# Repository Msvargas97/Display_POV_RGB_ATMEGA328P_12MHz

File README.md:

Display_POV_RGB_ATMEGA328P_12MHz
Control de display POV RGB v1.1 + Codigo Arduino+Bootloader V-USB

 Código C++ para Proyecto de grado - Tecnico Profesional en Electrónica -UDI

 ALGORITMO
  
  Los pasos para realización del código son los siguientes:
  
  0.Esperar que el sensor de efecto Hall indique el punto de partida de visualización   
  
  1.Se encienden los LEDs según los bits correspondientes de un número en binario
  que hace referencia a una columna de cualquier caracter, ya sea una image,numeros o letras.
  
  2.Gracias a que el timer esta configurado como comparador se asigna un periodo, el cual sera el tiempo que permaneceran
  encendida la columna de LEDs del paso anterior.
  
  3.Apagar los LEDs y repetir el algoritmo desde el paso 0.
  
   Posteriormente se tiene caracteristicas extras que se añaden en cualquiera de los pasos
   mencionados anteriormente segun sea su función,por ejemplo escoger el color de los LEDs
   esto se logra enviando un '1' lógico a la base del transistor que controla el color deseado,
   dicha caracteristica se implemento en el paso 1.

Caracteristicas:

Posee tres modos de operación:
-Modo frases ingresadas por Bluetooth o comunicacion serial.
-Modo visualizador de imagenes cargadas desde la EEPROM
-Modo reloj digital

  Elaborado por Michael Vargas
  
  2015
  
  msvargas97@gmail.com
  
  Open Source GitHub: https://github.com/Msvargas97/Display_POV_RGB_ATMEGA328P_12MHz
  
  Créditos al MiniPOV4 de Adrafuit, por el bootloader y el software para cargar imagenes.
  
  https://github.com/adafruit/Adafruit-MiniPOV4-Kit

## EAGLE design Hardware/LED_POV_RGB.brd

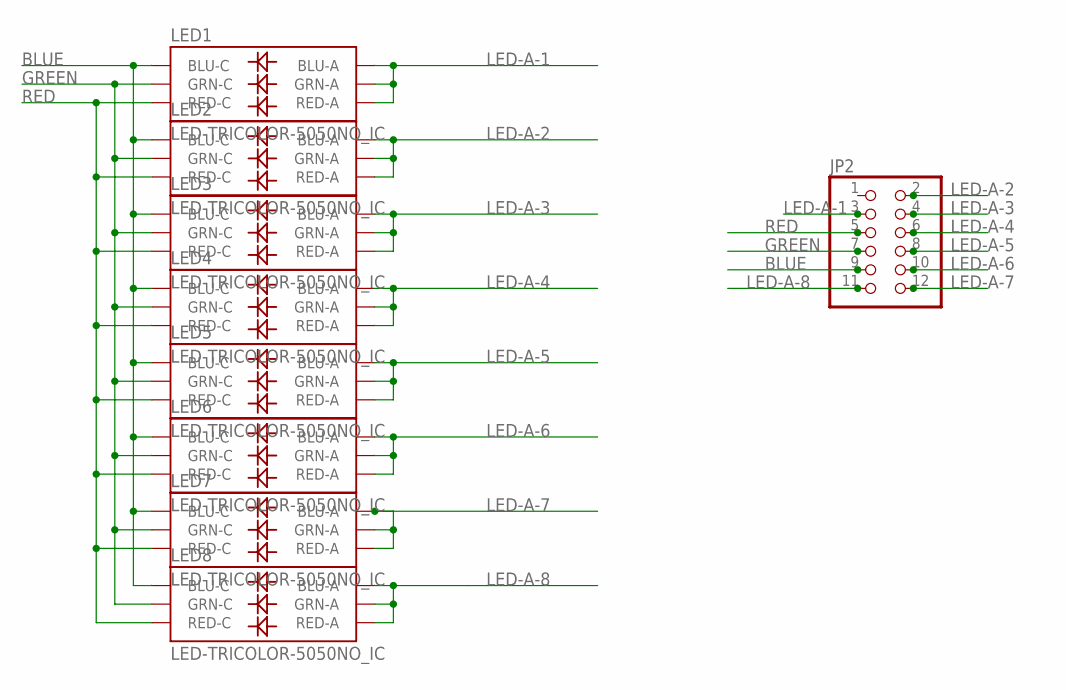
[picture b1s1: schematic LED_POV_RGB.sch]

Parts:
JP2: PINHD-2X6; 2X06
LED1, LED2, LED3, LED4, LED5, LED6, LED7, LED8: LED-TRICOLOR-5050NO_IC; LED-TRICOLOR-5050

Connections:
BLUE: JP2.9, LED1.4 (BLU-C), LED2.4 (BLU-C), LED3.4 (BLU-C), LED4.4 (BLU-C), LED5.4 (BLU-C), LED6.4 (BLU-C), LED7.4 (BLU-C), LED8.4 (BLU-C)
GREEN: JP2.7, LED1.6 (GRN-C), LED2.6 (GRN-C), LED3.6 (GRN-C), LED4.6 (GRN-C), LED5.6 (GRN-C), LED6.6 (GRN-C), LED7.6 (GRN-C), LED8.6 (GRN-C)
LED-A-1: JP2.3, LED1.1 (GRN-A), LED1.2 (RED-A), LED1.3 (BLU-A)
LED-A-2: JP2.2, LED2.1 (GRN-A), LED2.2 (RED-A), LED2.3 (BLU-A)
LED-A-3: JP2.4, LED3.1 (GRN-A), LED3.2 (RED-A), LED3.3 (BLU-A)
LED-A-4: JP2.6, LED4.1 (GRN-A), LED4.2 (RED-A), LED4.3 (BLU-A)
LED-A-5: JP2.8, LED5.1 (GRN-A), LED5.2 (RED-A), LED5.3 (BLU-A)
LED-A-6: JP2.10, LED6.1 (GRN-A), LED6.2 (RED-A), LED6.3 (BLU-A)
LED-A-7: JP2.12, LED7.1 (GRN-A), LED7.2 (RED-A), LED7.3 (BLU-A)
LED-A-8: JP2.11, LED8.1 (GRN-A), LED8.2 (RED-A), LED8.3 (BLU-A)
RED: JP2.5, LED1.5 (RED-C), LED2.5 (RED-C), LED3.5 (RED-C), LED4.5 (RED-C), LED5.5 (RED-C), LED6.5 (RED-C), LED7.5 (RED-C), LED8.5 (RED-C)

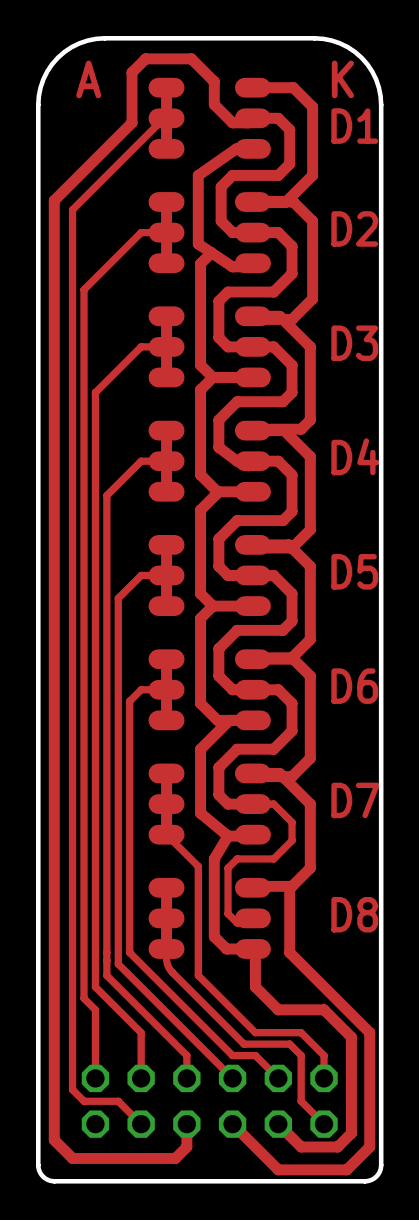
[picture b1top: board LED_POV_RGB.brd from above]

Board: 2 copper layers, 19.1 x 63.5 mm, 9 parts (0 on the bottom side), 11 nets.

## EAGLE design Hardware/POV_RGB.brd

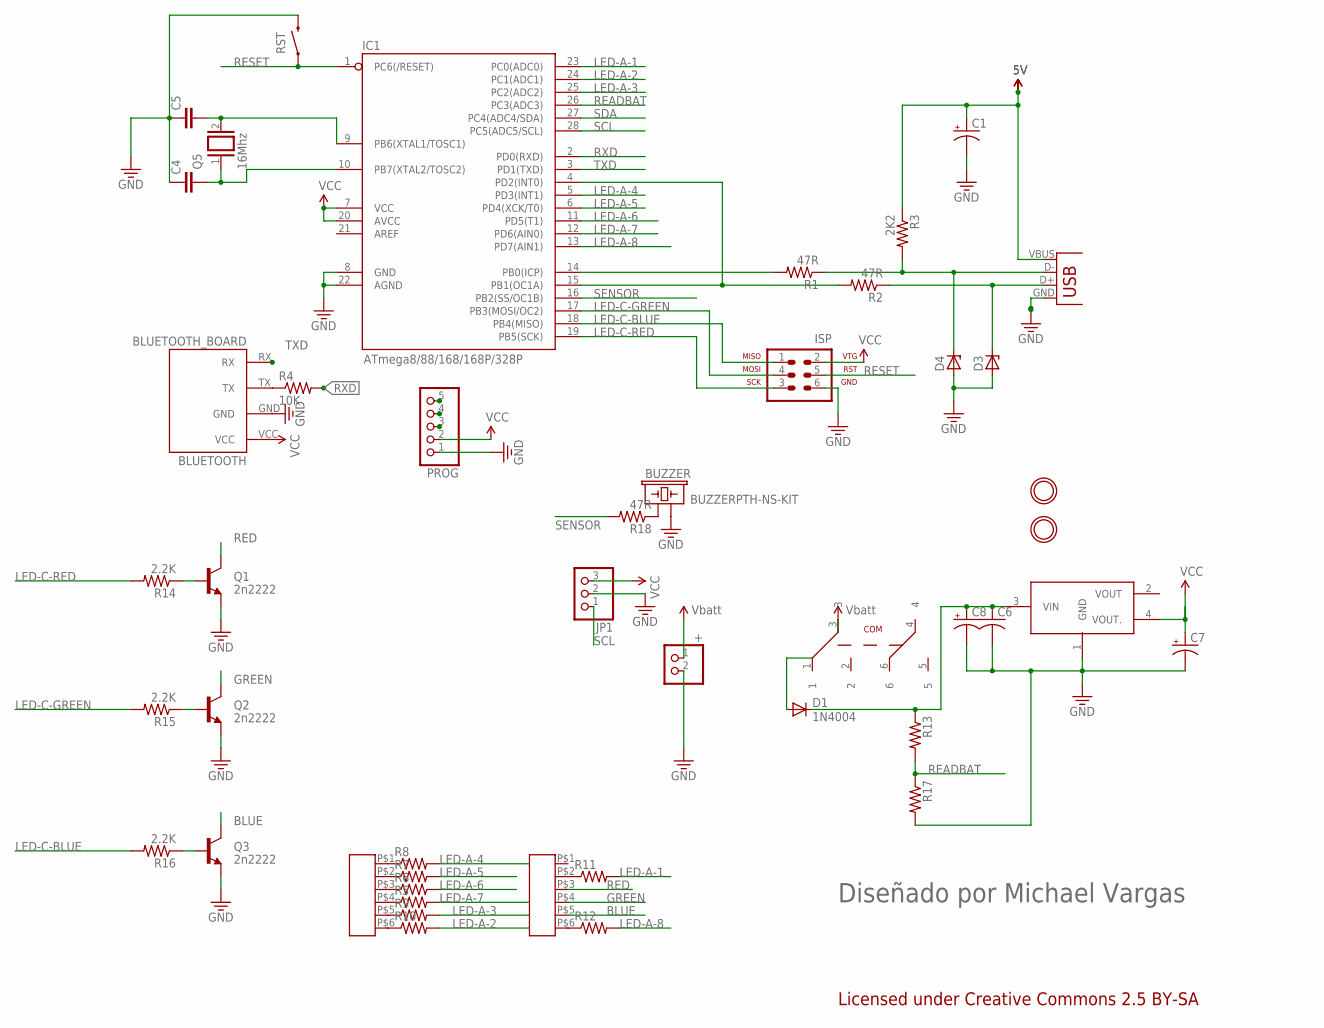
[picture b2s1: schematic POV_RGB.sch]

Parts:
5V: LD1117S50TR; SOT223
+: HEADER-1X2; 1X02_OVAL
BLUETOOTH: BLUETOOTH_BOARD; BT_BOARD_FOOTPRINT
BUZZER: BUZZERPTH-NS-KIT; BUZZER-12MM-NS-KIT
C1, C7, C8: CPOL-USD; PANASONIC_D
C4, C5: CAPPTH2; CAP-PTH-SMALL2
C6: C-USC1206; C1206
D1: 1N4004; DO41-10
D3, D4: ZENER-DIODEDO34-7; DO34Z7
IC1: ATmega8/88/168/168P/328P; DIL28-3
ISP: AVR-ISP-6
JP1: PINHD-1X3; 1X03
PROG: PINHD-1X5; 1X05
Q1, Q2, Q3: 2n2222; TO-92-AMMO
Q5: 16Mhz; QS
R1, R2: 47R; 0207/9
R3: 2K2; 0207/9
R4: 10K; R0805
R5, R6, R7, R8, R9, R10, R11, R12, R13, R17: R-US_R0805; R0805
R14, R15, R16: 2.2K; R0805
R18: 47R; R0805
RST: SWITCH-MOMENTARY-2SMD-1101NE; TACTILE-SWITCH-1101NE
U$2, U$4: MOUNTINGHOLE2.5_THICK; MOUNTINGHOLE_2.5_PLATED_THICK
U$3, U$5: SMD_HEADER6
U$6: TL2285
USB: USBPTH; USB-B-PTH

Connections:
3.3V: +.1, U$6.3
5V: C1.+, R3.1, USB.VBUS
BLUE: Q3.3 (C), U$5.P$5
GND: 5V.1 (GND), +.2, BLUETOOTH.GND, BUZZER.- (2), C1.-, C4.1, C5.1, C6.2, C7.-, C8.-, D3.A, D4.A, IC1.8 (GND), IC1.22 (AGND), ISP.6 (GND), JP1.2, PROG.1, Q1.1 (E), Q2.1 (E), Q3.1 (E), R17.2, RST.2, USB.GND, USB.S1, USB.S2
GREEN: Q2.3 (C), U$5.P$4
LED-A-1: IC1.23 (PC0(ADC0)), R11.2
LED-A-2: IC1.24 (PC1(ADC1)), R10.2
LED-A-3: IC1.25 (PC2(ADC2)), R9.2
LED-A-4: IC1.5 (PD3(INT1)), R8.2
LED-A-5: IC1.6 (PD4(XCK/T0)), R7.2
LED-A-6: IC1.11 (PD5(T1)), R6.2
LED-A-7: IC1.12 (PD6(AIN0)), R5.2
LED-A-8: IC1.13 (PD7(AIN1)), R12.2
LED-C-BLUE: IC1.18 (PB4(MISO)), ISP.1 (MISO), R16.2
LED-C-GREEN: IC1.17 (PB3(MOSI/OC2)), ISP.4 (MOSI), R15.2
LED-C-RED: IC1.19 (PB5(SCK)), ISP.3 (SCK), R14.2
unnamed: R5.1, U$3.P$4
unnamed: 5V.3 (VIN), C6.1, C8.+, D1.C, R13.1
unnamed: D4.C, R1.1, R3.2, USB.D-
unnamed: D3.C, R2.1, USB.D+
unnamed: R6.1, U$3.P$3
unnamed: R7.1, U$3.P$2
unnamed: IC1.14 (PB0(ICP)), R1.2
unnamed: IC1.4 (PD2(INT0)), IC1.15 (PB1(OC1A)), R2.2
unnamed: C5.2, IC1.9 (PB6(XTAL1/TOSC1)), Q5.2
unnamed: R8.1, U$3.P$1
unnamed: R9.1, U$3.P$5
unnamed: R10.1, U$3.P$6
unnamed: R11.1, U$5.P$2
unnamed: R12.1, U$5.P$6
unnamed: BUZZER.+ (1), R18.1
unnamed: Q1.2 (B), R14.1
unnamed: Q2.2 (B), R15.1
unnamed: Q3.2 (B), R16.1
unnamed: C4.2, IC1.10 (PB7(XTAL2/TOSC2)), Q5.1
unnamed: D1.A, U$6.1
unnamed: BLUETOOTH.TX, R4.1
READBAT: IC1.26 (PC3(ADC3)), R13.2, R17.1
RED: Q1.3 (C), U$5.P$3
RESET: IC1.1 (PC6(/RESET)), ISP.5 (RST), PROG.5, RST.1
RXD: IC1.2 (PD0(RXD)), PROG.4, R4.2
SCL: IC1.28 (PC5(ADC5/SCL)), JP1.1
SDA: IC1.27 (PC4(ADC4/SDA))
SENSOR: IC1.16 (PB2(SS/OC1B)), R18.2
TXD: BLUETOOTH.RX, IC1.3 (PD1(TXD)), PROG.3
VCC: 5V.4 (VOUT.), BLUETOOTH.VCC, C7.+, IC1.7 (VCC), IC1.20 (AVCC), ISP.2 (VTG), JP1.3, PROG.2

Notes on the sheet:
Licensed under Creative Commons 2.5 BY-SA
Diseñado por Michael Vargas

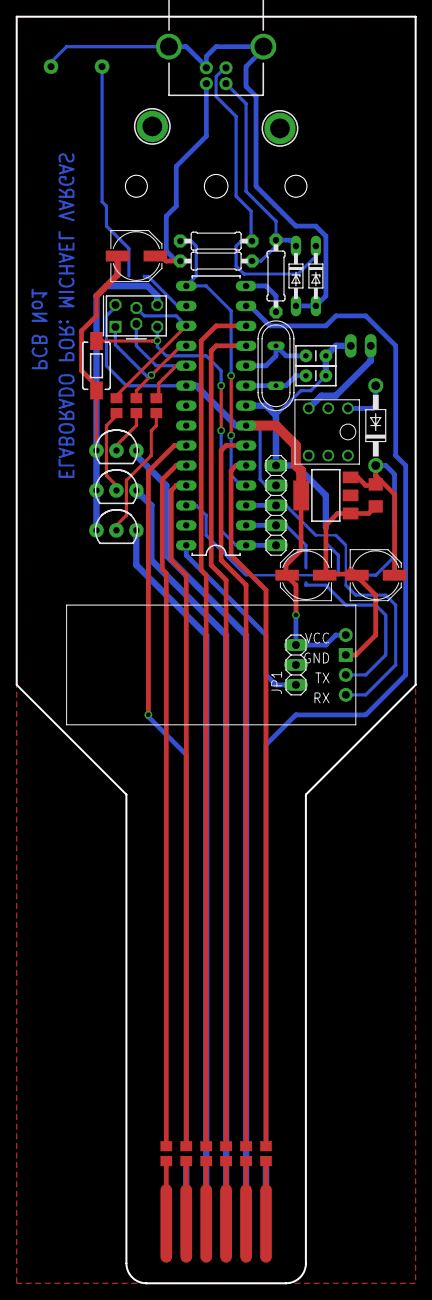
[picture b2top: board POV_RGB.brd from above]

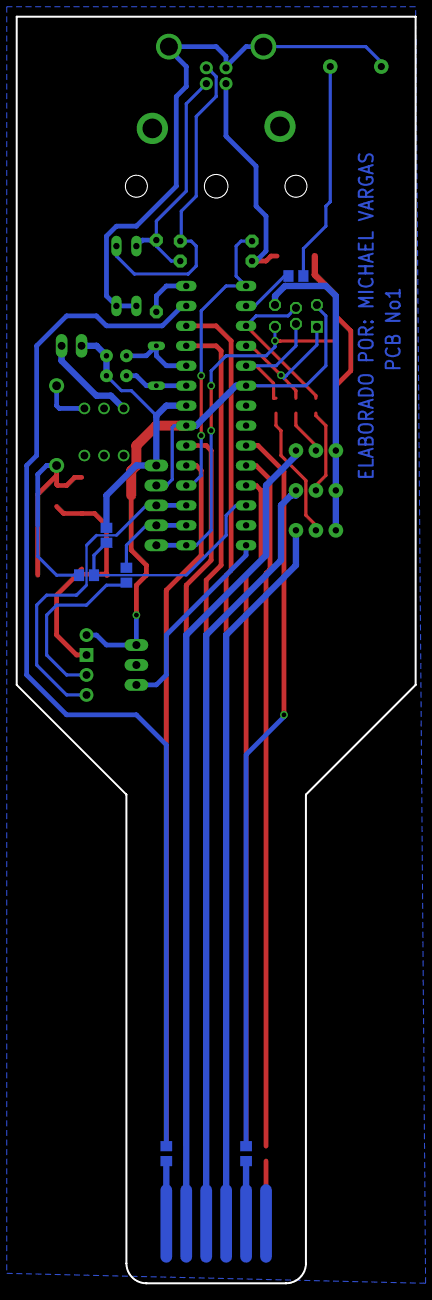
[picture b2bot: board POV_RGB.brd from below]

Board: 2 copper layers, 50.8 x 161.3 mm, 46 parts (7 on the bottom side), 45 nets.

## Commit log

2015-09-27 :tada: Added .gitattributes & .gitignore files
2015-09-27 initi v1.0
    Initial Version
    -Source code base:
    https://github.com/adafruit/Adafruit-MiniPOV4-Kit
    Thanks!
2015-10-12 README.md
    Descripción del proyecto display POV RGB.
    Michael Vargas
    Open Source
2015-10-12 Código debuggeado v1.1
2015-10-13 Archivos Eagle
    Añadido esquematicos y boards para la elaboración de las PCBs.
2015-11-19 Código POV RGB Depurado Full
    Es importante tener un punto de inicio con algún sensor de efecto hall o
    con emisor y receptor infrarojo

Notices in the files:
parts and their libraries:
SparkFun-LED: Licensing: Creative Commons ShareAlike 4.0 International - https://creativecommons.org/licenses/by-sa/4.0
microbuilder: This work is placed in the public domain, and may be freely used for commercial and non-commercial work with the following conditions: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
